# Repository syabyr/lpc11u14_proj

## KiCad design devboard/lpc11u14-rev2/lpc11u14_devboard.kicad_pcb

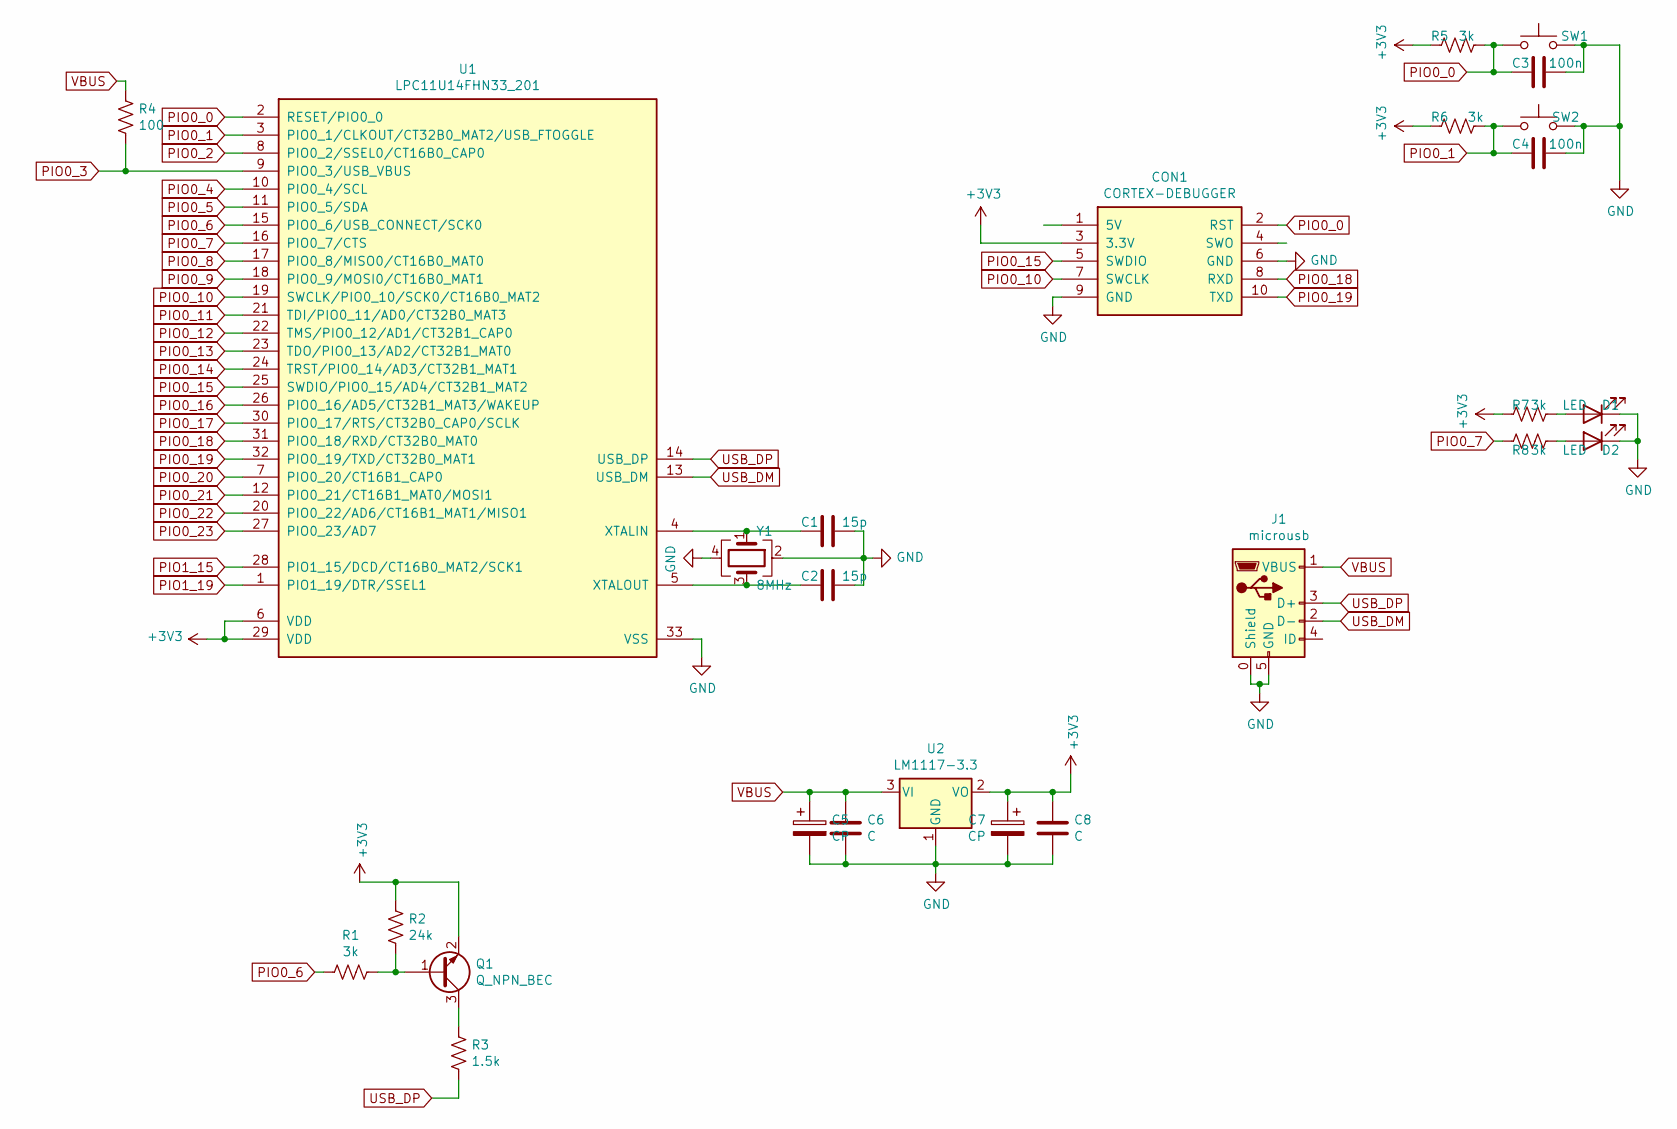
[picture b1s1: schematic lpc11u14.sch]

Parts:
C1, C2: 15p; C_0603_1608Metric
C3, C4: 100n; C_0603_1608Metric
C5, C7: CP; CP_EIA-3528-21_Kemet-B_Pad1.50x2.35mm_HandSolder
C6, C8: C; C_0603_1608Metric_Pad1.08x0.95mm_HandSolder
CON1: CORTEX-DEBUGGER; debugger_2x05_P1.27mm_Vertical
D1, D2: LED; LED_0805_2012Metric
J1: microusb; MICRO-USB_MICRO-USB-17
Q1: Q_NPN_BEC; SOT-23
R1, R5, R6, R7, R8: 3k; R_0603_1608Metric
R2: 24k; R_0603_1608Metric
R3: 1.5k; R_0603_1608Metric
R4: 100; R_0603_1608Metric
SW1, SW2: SW_Push; turtlekey
U1: LPC11U14FHN33_201; SOT865-1_N
U2: LM1117-3.3; SOT-223-3_TabPin2
Y1: 8MHz; Crystal_SMD_3225-4Pin_3.2x2.5mm

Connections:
+3V3: C7.1, C8.1, CON1.3 (3.3V), Q1.2 (E), R2.2, R5.2, R6.2, R7.2, U1.6 (VDD), U1.29 (VDD), U2.2 (VO); also elsewhere on the board
GND: C1.1, C2.1, C3.1, C4.1, C5.2, C6.2, C7.2, C8.2, CON1.6 (GND), CON1.9 (GND), D1.1 (K), D2.1 (K), J1.0 (Shield), J1.5 (GND), SW1.2, SW2.2, U1.33 (VSS), U2.1 (GND), Y1.2, Y1.4; also elsewhere on the board
unnamed: C1.2, U1.4 (XTALIN), Y1.1
unnamed: C2.2, U1.5 (XTALOUT), Y1.3
unnamed: D1.2 (A), R7.1
unnamed: D2.2 (A), R8.1
unnamed: Q1.1 (B), R1.1, R2.1
unnamed: Q1.3 (C), R3.2
PIO0_0: C3.2, CON1.2 (RST), R5.1, SW1.1, U1.2 (RESET/PIO0_0); also elsewhere on the board
PIO0_1: C4.2, R6.1, SW2.1, U1.3 (PIO0_1/CLKOUT/CT32B0_MAT2/USB_FTOGGLE); also elsewhere on the board
PIO0_2: U1.8 (PIO0_2/SSEL0/CT16B0_CAP0); also elsewhere on the board
PIO0_3: R4.1, U1.9 (PIO0_3/USB_VBUS); also elsewhere on the board
PIO0_4: U1.10 (PIO0_4/SCL); also elsewhere on the board
PIO0_5: U1.11 (PIO0_5/SDA); also elsewhere on the board
PIO0_6: R1.2, U1.15 (PIO0_6/USB_CONNECT/SCK0); also elsewhere on the board
PIO0_7: R8.2, U1.16 (PIO0_7/CTS); also elsewhere on the board
PIO0_8: U1.17 (PIO0_8/MISO0/CT16B0_MAT0); also elsewhere on the board
PIO0_9: U1.18 (PIO0_9/MOSI0/CT16B0_MAT1); also elsewhere on the board
PIO0_10: CON1.7 (SWCLK), U1.19 (SWCLK/PIO0_10/SCK0/CT16B0_MAT2); also elsewhere on the board
PIO0_11: U1.21 (TDI/PIO0_11/AD0/CT32B0_MAT3); also elsewhere on the board
PIO0_12: U1.22 (TMS/PIO0_12/AD1/CT32B1_CAP0); also elsewhere on the board
PIO0_13: U1.23 (TDO/PIO0_13/AD2/CT32B1_MAT0); also elsewhere on the board
PIO0_14: U1.24 (TRST/PIO0_14/AD3/CT32B1_MAT1); also elsewhere on the board
PIO0_15: CON1.5 (SWDIO), U1.25 (SWDIO/PIO0_15/AD4/CT32B1_MAT2); also elsewhere on the board
PIO0_16: U1.26 (PIO0_16/AD5/CT32B1_MAT3/WAKEUP); also elsewhere on the board
PIO0_17: U1.30 (PIO0_17/RTS/CT32B0_CAP0/SCLK); also elsewhere on the board
PIO0_18: CON1.8 (RXD), U1.31 (PIO0_18/RXD/CT32B0_MAT0); also elsewhere on the board
PIO0_19: CON1.10 (TXD), U1.32 (PIO0_19/TXD/CT32B0_MAT1); also elsewhere on the board
PIO0_20: U1.7 (PIO0_20/CT16B1_CAP0); also elsewhere on the board
PIO0_21: U1.12 (PIO0_21/CT16B1_MAT0/MOSI1); also elsewhere on the board
PIO0_22: U1.20 (PIO0_22/AD6/CT16B1_MAT1/MISO1); also elsewhere on the board
PIO0_23: U1.27 (PIO0_23/AD7); also elsewhere on the board
PIO1_15: U1.28 (PIO1_15/DCD/CT16B0_MAT2/SCK1); also elsewhere on the board
PIO1_19: U1.1 (PIO1_19/DTR/SSEL1); also elsewhere on the board
USB_DM: J1.2 (D-), U1.13 (USB_DM)
USB_DP: J1.3 (D+), R3.1, U1.14 (USB_DP)
VBUS: C5.1, C6.1, J1.1 (VBUS), R4.2, U2.3 (VI); also elsewhere on the board

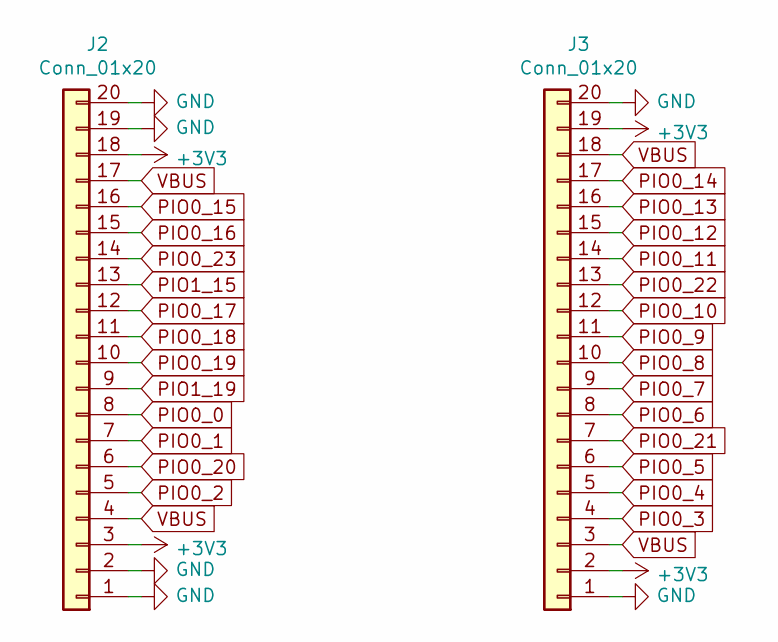
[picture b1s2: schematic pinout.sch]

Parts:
J2, J3: Conn_01x20; PinHeader_1x20_P2.54mm_Vertical

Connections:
+3V3: J2.3, J2.18, J3.2, J3.19; also elsewhere on the board
GND: J2.1, J2.2, J2.19, J2.20, J3.1, J3.20; also elsewhere on the board
PIO0_0: J2.8; also elsewhere on the board
PIO0_1: J2.7; also elsewhere on the board
PIO0_2: J2.5; also elsewhere on the board
PIO0_3: J3.4; also elsewhere on the board
PIO0_4: J3.5; also elsewhere on the board
PIO0_5: J3.6; also elsewhere on the board
PIO0_6: J3.8; also elsewhere on the board
PIO0_7: J3.9; also elsewhere on the board
PIO0_8: J3.10; also elsewhere on the board
PIO0_9: J3.11; also elsewhere on the board
PIO0_10: J3.12; also elsewhere on the board
PIO0_11: J3.14; also elsewhere on the board
PIO0_12: J3.15; also elsewhere on the board
PIO0_13: J3.16; also elsewhere on the board
PIO0_14: J3.17; also elsewhere on the board
PIO0_15: J2.16; also elsewhere on the board
PIO0_16: J2.15; also elsewhere on the board
PIO0_17: J2.12; also elsewhere on the board
PIO0_18: J2.11; also elsewhere on the board
PIO0_19: J2.10; also elsewhere on the board
PIO0_20: J2.6; also elsewhere on the board
PIO0_21: J3.7; also elsewhere on the board
PIO0_22: J3.13; also elsewhere on the board
PIO0_23: J2.14; also elsewhere on the board
PIO1_15: J2.13; also elsewhere on the board
PIO1_19: J2.9; also elsewhere on the board
VBUS: J2.4, J2.17, J3.3, J3.18; also elsewhere on the board

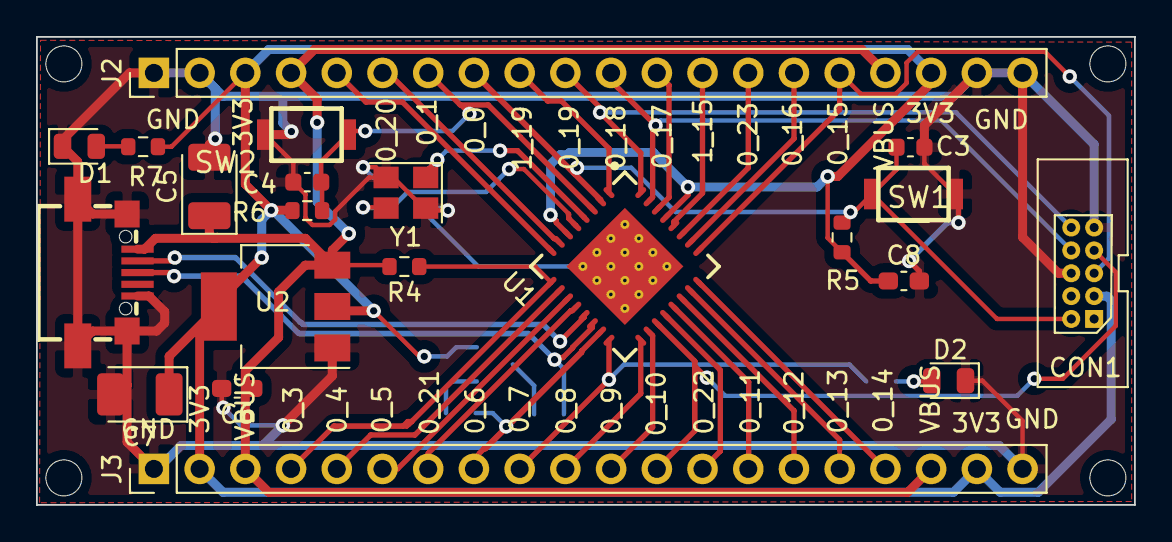
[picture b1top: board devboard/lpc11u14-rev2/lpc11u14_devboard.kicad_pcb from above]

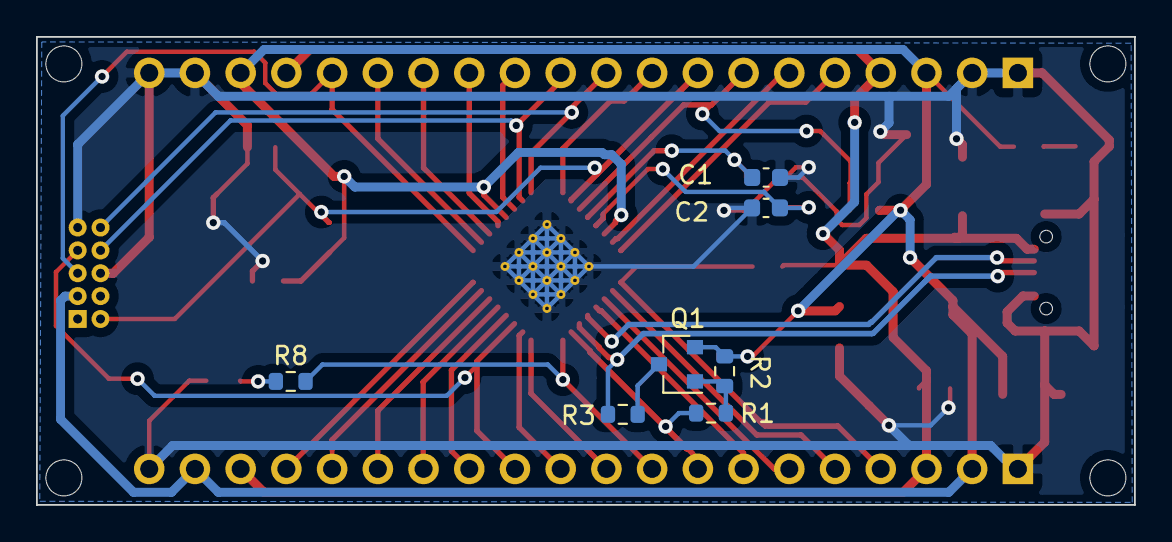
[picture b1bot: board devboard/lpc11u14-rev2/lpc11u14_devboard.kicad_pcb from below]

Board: 2 copper layers, 61.0 x 26.0 mm, 28 parts (7 on the bottom side), 37 nets.

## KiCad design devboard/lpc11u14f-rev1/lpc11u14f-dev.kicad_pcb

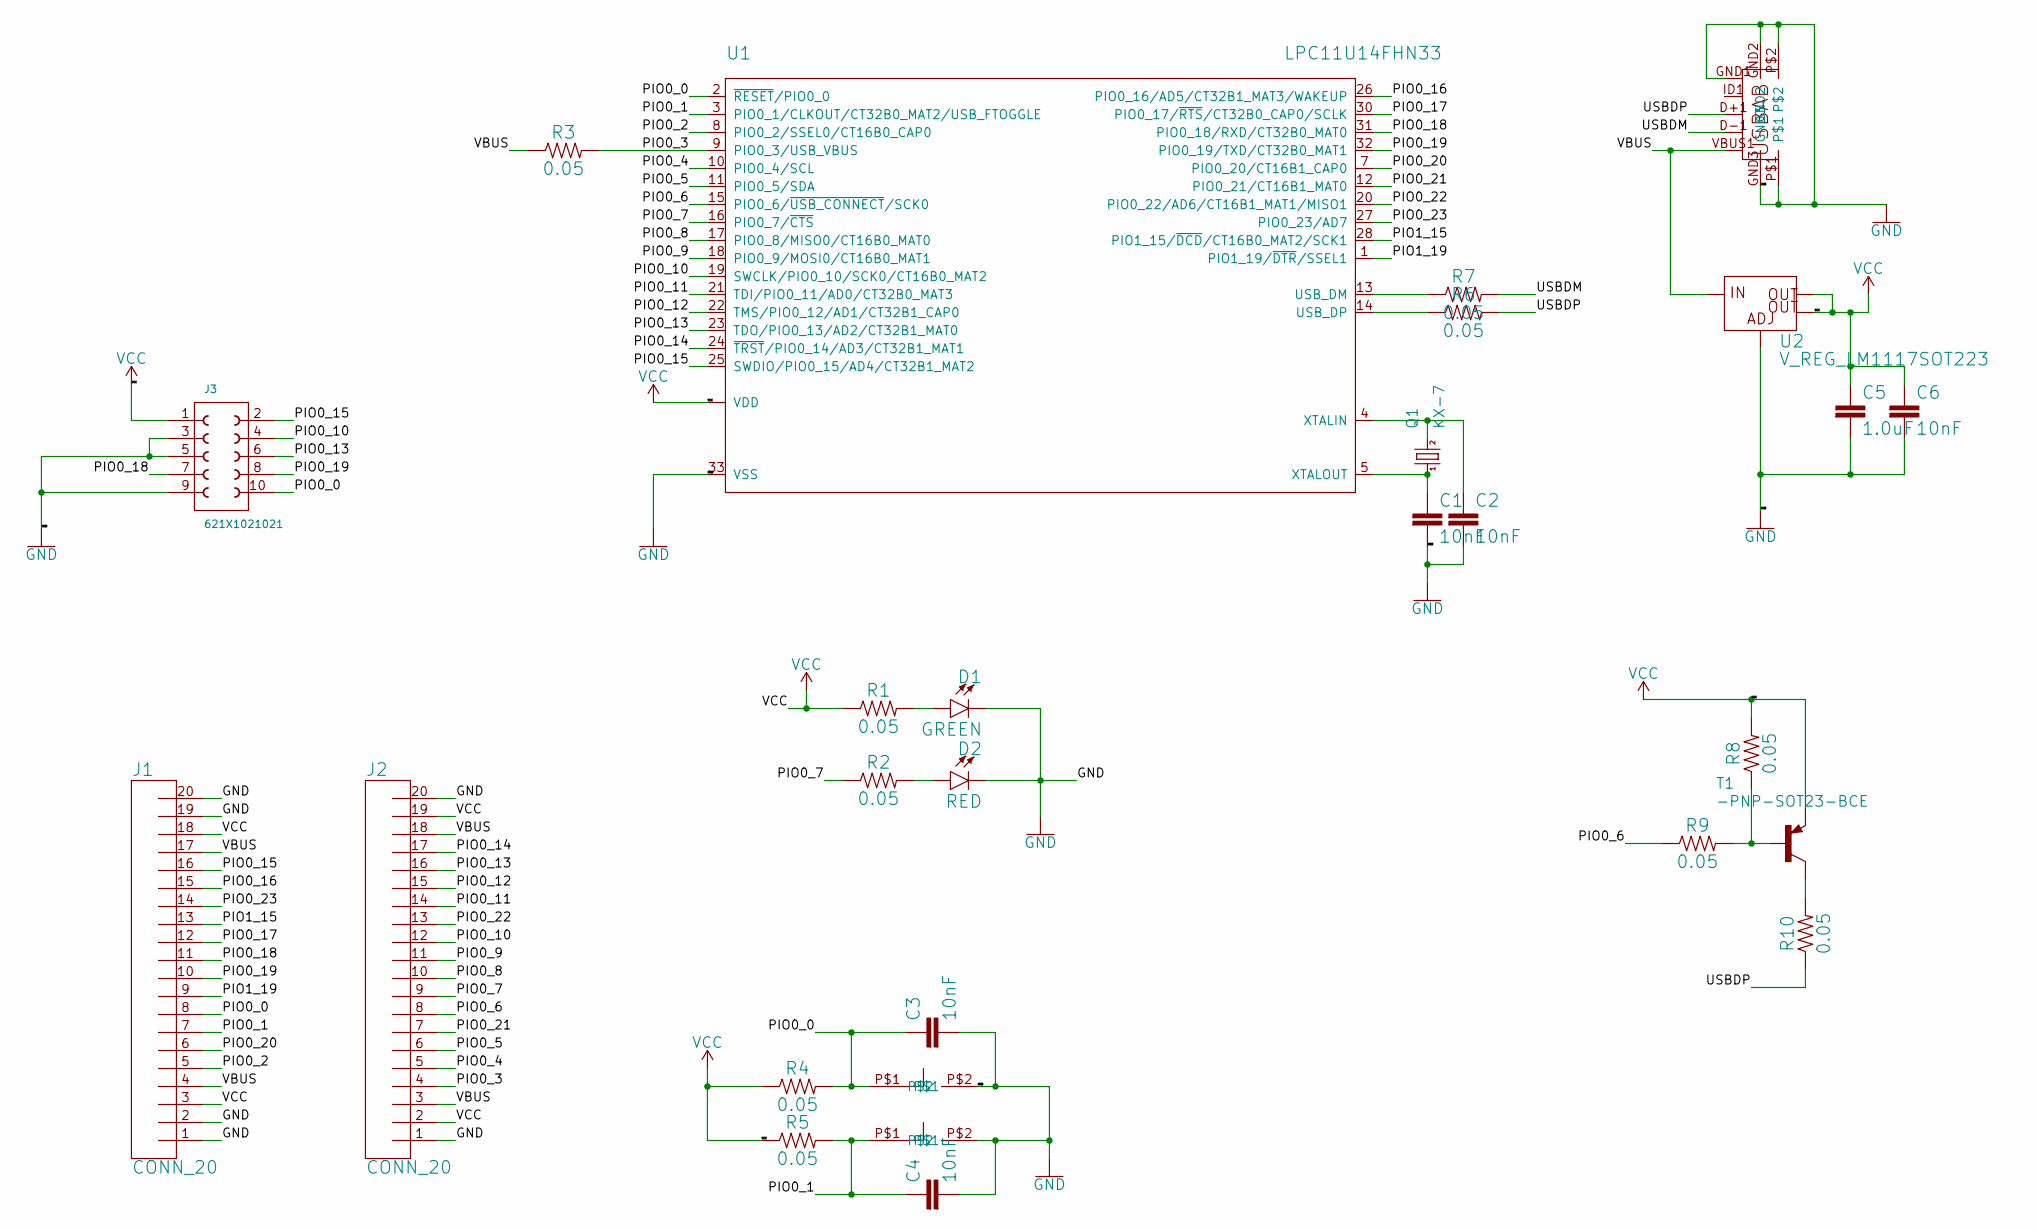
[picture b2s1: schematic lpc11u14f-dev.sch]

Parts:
C1, C2, C3, C4, C6: 10nF; 0603
C5: 1.0uF; 1206
D1: GREEN; LED-0603
D2: RED; LED-0603
J1, J2: CONN_20; 1X20
J3: 621X1021021
Q1: KX-7; 3.2X2.5_KX-7
R1, R2, R3, R4, R5, R6, R7, R8, R9, R10: 0.05; 0603
T1: -PNP-SOT23-BCE; SOT23-BCE
U1: LPC11U14FHN33; SOT-HVQFN33
U2: V_REG_LM1117SOT223; SOT223
U$1: USB_GND; USB-MICRO-SMD
U$2, U$3: QTKEY

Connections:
GND: C1.2, C2.2, C3.2, C4.2, C5.2, C6.2, D1.C, D2.C, J1.1, J1.2, J1.19, J1.20, J2.1, J2.20, J3.3 (2), J3.5 (3), J3.9 (5), U1.33 (VSS), U2.1 (ADJ), U$1.GND1 (GND), U$1.GND2, U$1.GND3, U$1.P$1, U$1.P$2, U$2.P$2, U$3.P$2
unnamed: D1.A, R1.2
unnamed: D2.A, R2.2
unnamed: R8.1, R9.2, T1.B
unnamed: R10.2, T1.C
unnamed: C1.1, Q1.1, U1.5 (XTALOUT)
unnamed: C2.1, Q1.3 (2), U1.4 (XTALIN)
PIO0_0: C3.1, J1.8, J3.10 (6), R4.2, U1.2 (~RESET~/PIO0_0), U$2.P$1
PIO0_1: C4.1, J1.7, R5.2, U1.3 (PIO0_1/CLKOUT/CT32B0_MAT2/USB_FTOGGLE), U$3.P$1
PIO0_2: J1.5, U1.8 (PIO0_2/SSEL0/CT16B0_CAP0)
PIO0_3: J2.4, R3.2, U1.9 (PIO0_3/USB_VBUS)
PIO0_4: J2.5, U1.10 (PIO0_4/SCL)
PIO0_5: J2.6, U1.11 (PIO0_5/SDA)
PIO0_6: J2.8, R9.1, U1.15 (PIO0_6/~USB_CONNECT~/SCK0)
PIO0_7: J2.9, R2.1, U1.16 (PIO0_7/~CTS~)
PIO0_8: J2.10, U1.17 (PIO0_8/MISO0/CT16B0_MAT0)
PIO0_9: J2.11, U1.18 (PIO0_9/MOSI0/CT16B0_MAT1)
PIO0_10: J2.12, J3.4 (9), U1.19 (SWCLK/PIO0_10/SCK0/CT16B0_MAT2)
PIO0_11: J2.14, U1.21 (TDI/PIO0_11/AD0/CT32B0_MAT3)
PIO0_12: J2.15, U1.22 (TMS/PIO0_12/AD1/CT32B1_CAP0)
PIO0_13: J2.16, J3.6 (8), U1.23 (TDO/PIO0_13/AD2/CT32B1_MAT0)
PIO0_14: J2.17, U1.24 (~TRST~/PIO0_14/AD3/CT32B1_MAT1)
PIO0_15: J1.16, J3.2 (10), U1.25 (SWDIO/PIO0_15/AD4/CT32B1_MAT2)
PIO0_16: J1.15, U1.26 (PIO0_16/AD5/CT32B1_MAT3/WAKEUP)
PIO0_17: J1.12, U1.30 (PIO0_17/~RTS~/CT32B0_CAP0/SCLK)
PIO0_18: J1.11, J3.7 (4), U1.31 (PIO0_18/RXD/CT32B0_MAT0)
PIO0_19: J1.10, J3.8 (7), U1.32 (PIO0_19/TXD/CT32B0_MAT1)
PIO0_20: J1.6, U1.7 (PIO0_20/CT16B1_CAP0)
PIO0_21: J2.7, U1.12 (PIO0_21/CT16B1_MAT0)
PIO0_22: J2.13, U1.20 (PIO0_22/AD6/CT16B1_MAT1/MISO1)
PIO0_23: J1.14, U1.27 (PIO0_23/AD7)
PIO1_15: J1.13, U1.28 (PIO1_15/~DCD~/CT16B0_MAT2/SCK1)
PIO1_19: J1.9, U1.1 (PIO1_19/~DTR~/SSEL1)
USBDM: R7.2, U$1.D-1 (D-)
USBDP: R6.2, R10.1, U$1.D+1 (D+)
USB_DM: R7.1, U1.13 (USB_DM)
USB_DP: R6.1, U1.14 (USB_DP)
VBUS: J1.4, J1.17, J2.3, J2.18, R3.1, U2.3 (IN), U$1.VBUS1 (VBUS)
VCC: C5.1, C6.1, J1.3, J1.18, J2.2, J2.19, J3.1, R1.1, R4.1, R5.1, R8.2, T1.E, U1.6 (VDD), U1.29 (VDD), U2.2 (OUT), U2.4 (OUT@1)

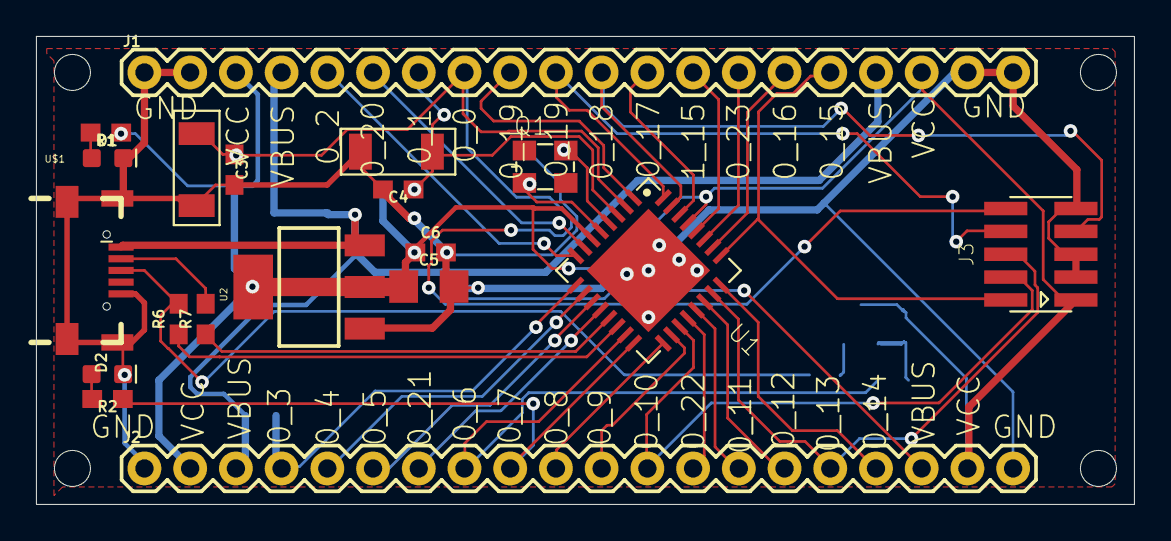
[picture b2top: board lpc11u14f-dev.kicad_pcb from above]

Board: 2 copper layers, 61.0 x 26.0 mm, 32 parts (0 on the bottom side), 39 nets.

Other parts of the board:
@HOLE0, @HOLE1, @HOLE2, @HOLE3: (no value)

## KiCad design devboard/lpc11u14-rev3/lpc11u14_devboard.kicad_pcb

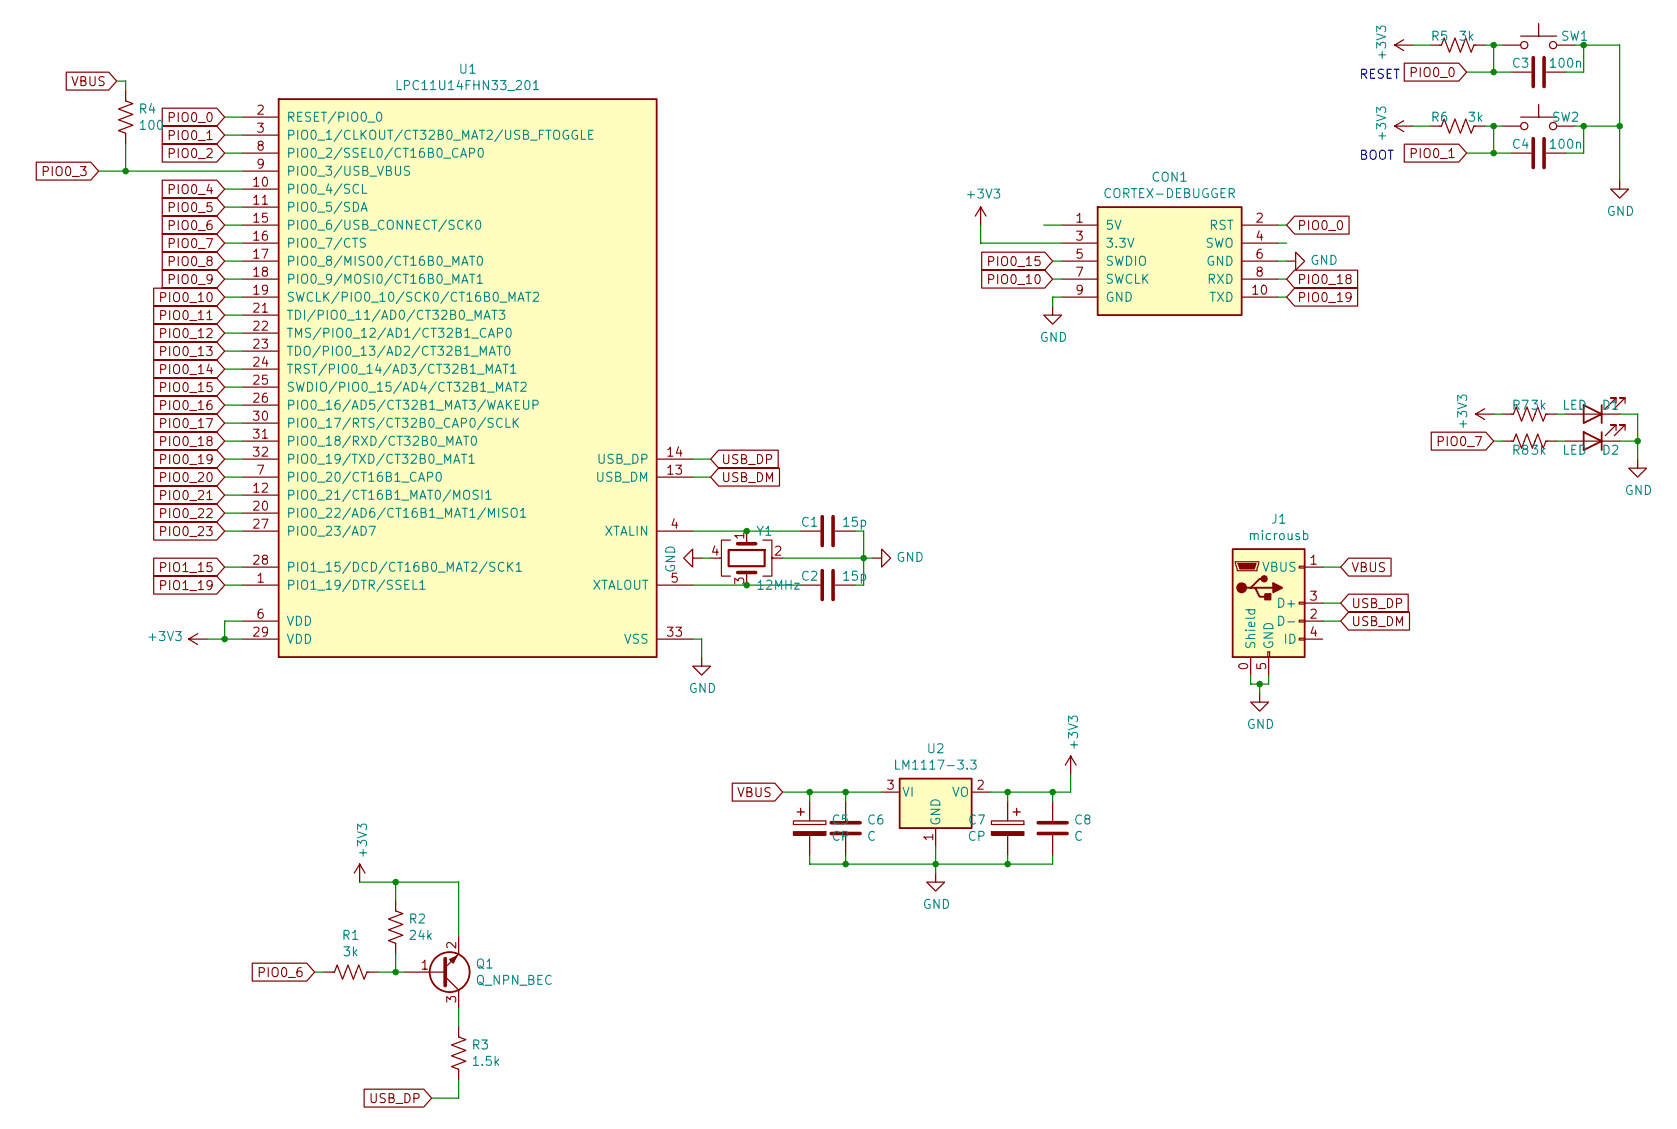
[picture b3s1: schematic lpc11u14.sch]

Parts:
C1, C2: 15p; C_0603_1608Metric
C3, C4: 100n; C_0603_1608Metric
C5, C7: CP; CP_EIA-3528-21_Kemet-B_Pad1.50x2.35mm_HandSolder
C6, C8: C; C_0603_1608Metric_Pad1.08x0.95mm_HandSolder
CON1: CORTEX-DEBUGGER; debugger_2x05_P1.27mm_Vertical
D1, D2: LED; LED_0805_2012Metric
J1: microusb; USB_Micro-B_Wuerth_629105150521_CircularHoles
Q1: Q_NPN_BEC; SOT-23
R1, R5, R6, R7, R8: 3k; R_0603_1608Metric
R2: 24k; R_0603_1608Metric
R3: 1.5k; R_0603_1608Metric
R4: 100; R_0603_1608Metric
SW1, SW2: SW_Push; turtlekey
U1: LPC11U14FHN33_201; SOT865-1_N
U2: LM1117-3.3; SOT-223-3_TabPin2
Y1: 12MHz; Crystal_SMD_3225-4Pin_3.2x2.5mm

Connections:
+3V3: C7.1, C8.1, CON1.3 (3.3V), Q1.2 (E), R2.2, R5.2, R6.2, R7.2, U1.6 (VDD), U1.29 (VDD), U2.2 (VO); also elsewhere on the board
GND: C1.1, C2.1, C3.1, C4.1, C5.2, C6.2, C7.2, C8.2, CON1.6 (GND), CON1.9 (GND), D1.1 (K), D2.1 (K), J1.0 (Shield), J1.5 (GND), SW1.2, SW2.2, U1.33 (VSS), U2.1 (GND), Y1.2, Y1.4; also elsewhere on the board
unnamed: C1.2, U1.4 (XTALIN), Y1.1
unnamed: C2.2, U1.5 (XTALOUT), Y1.3
unnamed 4: D1.2 (A), R7.1; also elsewhere on the board
unnamed 5: D2.2 (A), R8.1; also elsewhere on the board
unnamed: Q1.1 (B), R1.1, R2.1
unnamed: Q1.3 (C), R3.2
PIO0_0: C3.2, CON1.2 (RST), R5.1, SW1.1, U1.2 (RESET/PIO0_0); also elsewhere on the board
PIO0_1: C4.2, R6.1, SW2.1, U1.3 (PIO0_1/CLKOUT/CT32B0_MAT2/USB_FTOGGLE); also elsewhere on the board
PIO0_2: U1.8 (PIO0_2/SSEL0/CT16B0_CAP0); also elsewhere on the board
PIO0_3: R4.1, U1.9 (PIO0_3/USB_VBUS); also elsewhere on the board
PIO0_4: U1.10 (PIO0_4/SCL); also elsewhere on the board
PIO0_5: U1.11 (PIO0_5/SDA); also elsewhere on the board
PIO0_6: R1.2, U1.15 (PIO0_6/USB_CONNECT/SCK0); also elsewhere on the board
PIO0_7: R8.2, U1.16 (PIO0_7/CTS); also elsewhere on the board
PIO0_8: U1.17 (PIO0_8/MISO0/CT16B0_MAT0); also elsewhere on the board
PIO0_9: U1.18 (PIO0_9/MOSI0/CT16B0_MAT1); also elsewhere on the board
PIO0_10: CON1.7 (SWCLK), U1.19 (SWCLK/PIO0_10/SCK0/CT16B0_MAT2); also elsewhere on the board
PIO0_11: U1.21 (TDI/PIO0_11/AD0/CT32B0_MAT3); also elsewhere on the board
PIO0_12: U1.22 (TMS/PIO0_12/AD1/CT32B1_CAP0); also elsewhere on the board
PIO0_13: U1.23 (TDO/PIO0_13/AD2/CT32B1_MAT0); also elsewhere on the board
PIO0_14: U1.24 (TRST/PIO0_14/AD3/CT32B1_MAT1); also elsewhere on the board
PIO0_15: CON1.5 (SWDIO), U1.25 (SWDIO/PIO0_15/AD4/CT32B1_MAT2); also elsewhere on the board
PIO0_16: U1.26 (PIO0_16/AD5/CT32B1_MAT3/WAKEUP); also elsewhere on the board
PIO0_17: U1.30 (PIO0_17/RTS/CT32B0_CAP0/SCLK); also elsewhere on the board
PIO0_18: CON1.8 (RXD), U1.31 (PIO0_18/RXD/CT32B0_MAT0); also elsewhere on the board
PIO0_19: CON1.10 (TXD), U1.32 (PIO0_19/TXD/CT32B0_MAT1); also elsewhere on the board
PIO0_20: U1.7 (PIO0_20/CT16B1_CAP0); also elsewhere on the board
PIO0_21: U1.12 (PIO0_21/CT16B1_MAT0/MOSI1); also elsewhere on the board
PIO0_22: U1.20 (PIO0_22/AD6/CT16B1_MAT1/MISO1); also elsewhere on the board
PIO0_23: U1.27 (PIO0_23/AD7); also elsewhere on the board
PIO1_15: U1.28 (PIO1_15/DCD/CT16B0_MAT2/SCK1); also elsewhere on the board
PIO1_19: U1.1 (PIO1_19/DTR/SSEL1); also elsewhere on the board
USB_DM: J1.2 (D-), U1.13 (USB_DM); also elsewhere on the board
USB_DP: J1.3 (D+), R3.1, U1.14 (USB_DP); also elsewhere on the board
VBUS: C5.1, C6.1, J1.1 (VBUS), R4.2, U2.3 (VI); also elsewhere on the board

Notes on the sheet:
RESET
BOOT

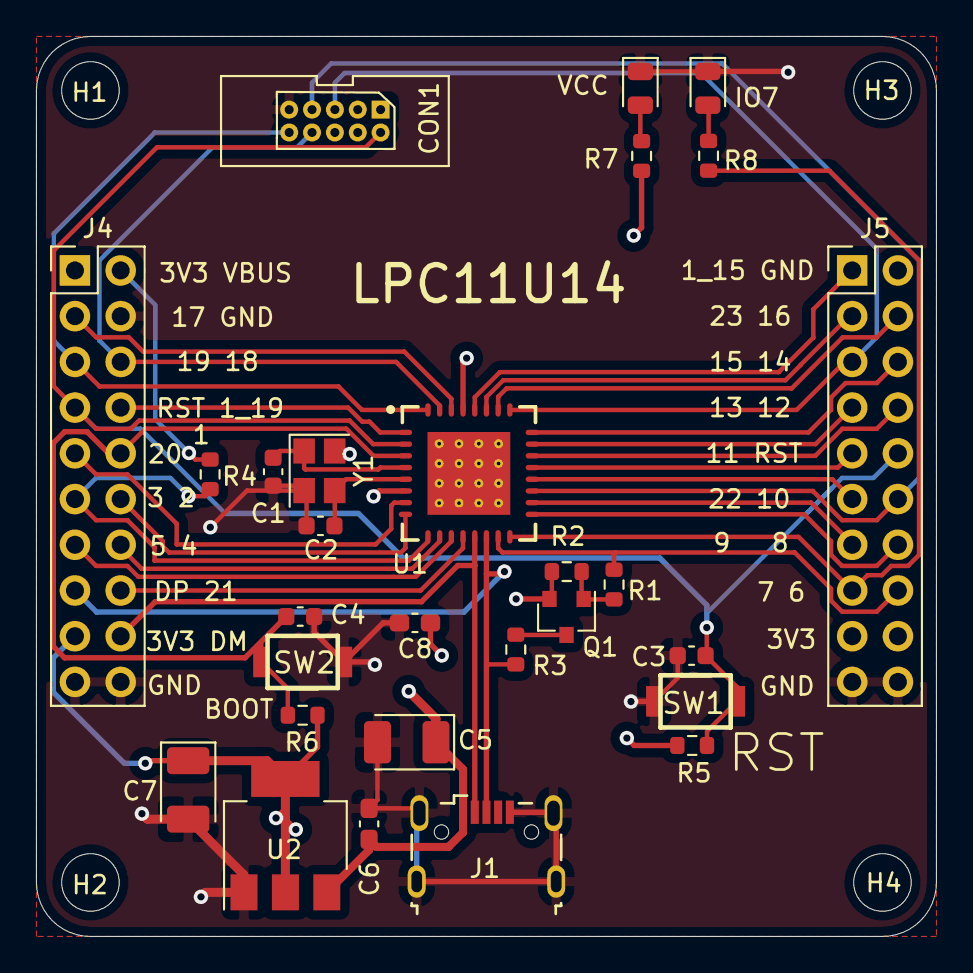
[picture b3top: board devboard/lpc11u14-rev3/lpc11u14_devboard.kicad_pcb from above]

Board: 4 copper layers, 50.0 x 50.0 mm, 32 parts (0 on the bottom side), 37 nets.

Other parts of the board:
H1, H2, H3, H4: MountingHole; MountingHole_3.2mm_M3_ISO7380
IO7: LED; LED_0805_2012Metric
J4, J5: Conn_02x10_Odd_Even; PinHeader_2x10_P2.54mm_Vertical
VCC: LED; LED_0805_2012Metric

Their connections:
+3V3: J4.1, J4.17, J5.17, J5.18; also elsewhere on the board
GND: IO7.1, J4.4, J4.19, J4.20, J5.2, J5.19, J5.20, VCC.1; also elsewhere on the board
unnamed 4: VCC.2; also elsewhere on the board
unnamed 5: IO7.2; also elsewhere on the board
PIO0_0: J4.7, J5.10; also elsewhere on the board
PIO0_1: J4.10; also elsewhere on the board
PIO0_2: J4.12; also elsewhere on the board
PIO0_3: J4.11; also elsewhere on the board
PIO0_4: J4.14; also elsewhere on the board
PIO0_5: J4.13; also elsewhere on the board
PIO0_6: J5.16; also elsewhere on the board
PIO0_7: J5.15; also elsewhere on the board
PIO0_8: J5.14; also elsewhere on the board
PIO0_9: J5.13; also elsewhere on the board
PIO0_10: J5.12; also elsewhere on the board
PIO0_11: J5.9; also elsewhere on the board
PIO0_12: J5.8; also elsewhere on the board
PIO0_13: J5.7; also elsewhere on the board
PIO0_14: J5.6; also elsewhere on the board
PIO0_15: J5.5; also elsewhere on the board
PIO0_16: J5.4; also elsewhere on the board
PIO0_17: J4.3; also elsewhere on the board
PIO0_18: J4.6; also elsewhere on the board
PIO0_19: J4.5; also elsewhere on the board
PIO0_20: J4.9; also elsewhere on the board
PIO0_21: J4.16; also elsewhere on the board
PIO0_22: J5.11; also elsewhere on the board
PIO0_23: J5.3; also elsewhere on the board
PIO1_15: J5.1; also elsewhere on the board
PIO1_19: J4.8; also elsewhere on the board
USB_DM: J4.18; also elsewhere on the board
USB_DP: J4.15; also elsewhere on the board
VBUS: J4.2; also elsewhere on the board

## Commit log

2021-01-10 rev1
2021-01-10 example
2021-01-12 add lpc21isp
2021-01-12 mymodify
2021-01-16 devboard rev2
2021-01-23 test firmware
2021-01-23 default 12MHz
2021-01-24 eval board example
2021-07-03 toolchain
2021-12-28 rev3
